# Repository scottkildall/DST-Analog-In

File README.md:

# DST-Analog-In

 Written by Scott Kildall

## Overview

[to be added]

### Hardware

The hardware is a number of circuit board, designed in Kicad, that can be manufactuered with some standard components.

#### License

CERN Open Hardware Licence Version 2 - Permissive

CERN-OHL-P-2.0

Other web pages for this license
https://www.ohwr.org/project/cernohl/wikis/Documents/CERN-OHL-version-2

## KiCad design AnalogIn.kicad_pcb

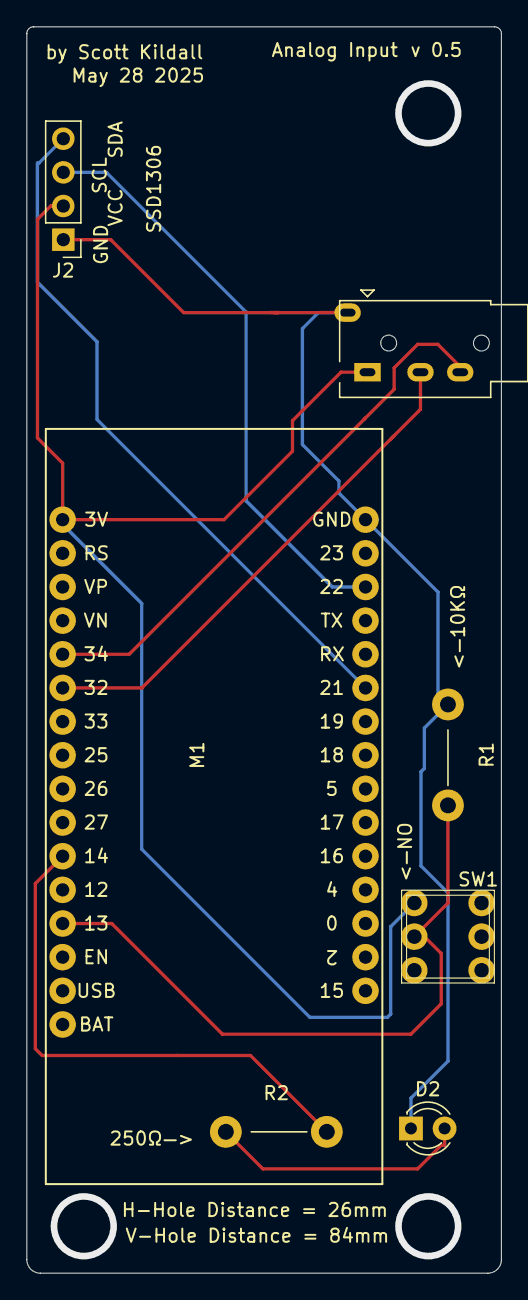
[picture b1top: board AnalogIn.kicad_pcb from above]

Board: 2 copper layers, 35.8 x 94.1 mm, 7 parts (0 on the bottom side), 9 nets.

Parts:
D2: LED; LED_D3.0mm_FlatTop
J1: AudioJack4; Jack_3.5mm_PJ320D_ThruHole
J2: Conn_01x04_Male; PinHeader_1x04_P2.54mm_Vertical
M1: LolinD32_v1
R1, R2: R; Resistor_TRT
SW1: SW_SPST; TPST_ThruHole_LatchingSwitch

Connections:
unnamed: D2.1, J1.S, J2.1, M1.32, R1.1
unnamed: D2.2, R2.1
unnamed: J1.R1, M1.11
unnamed: J1.R2, M1.12
unnamed: J1.T, J2.2, M1.16, SW1.1
unnamed: J2.3, M1.30
unnamed: J2.4, M1.27
unnamed: M1.4, R1.2, SW1.2
unnamed: M1.6, R2.2

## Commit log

2025-07-08 added .gitignore
2025-07-08 board design + gerbers, sorry no Readme yet
2025-07-08 ReadMe + license
